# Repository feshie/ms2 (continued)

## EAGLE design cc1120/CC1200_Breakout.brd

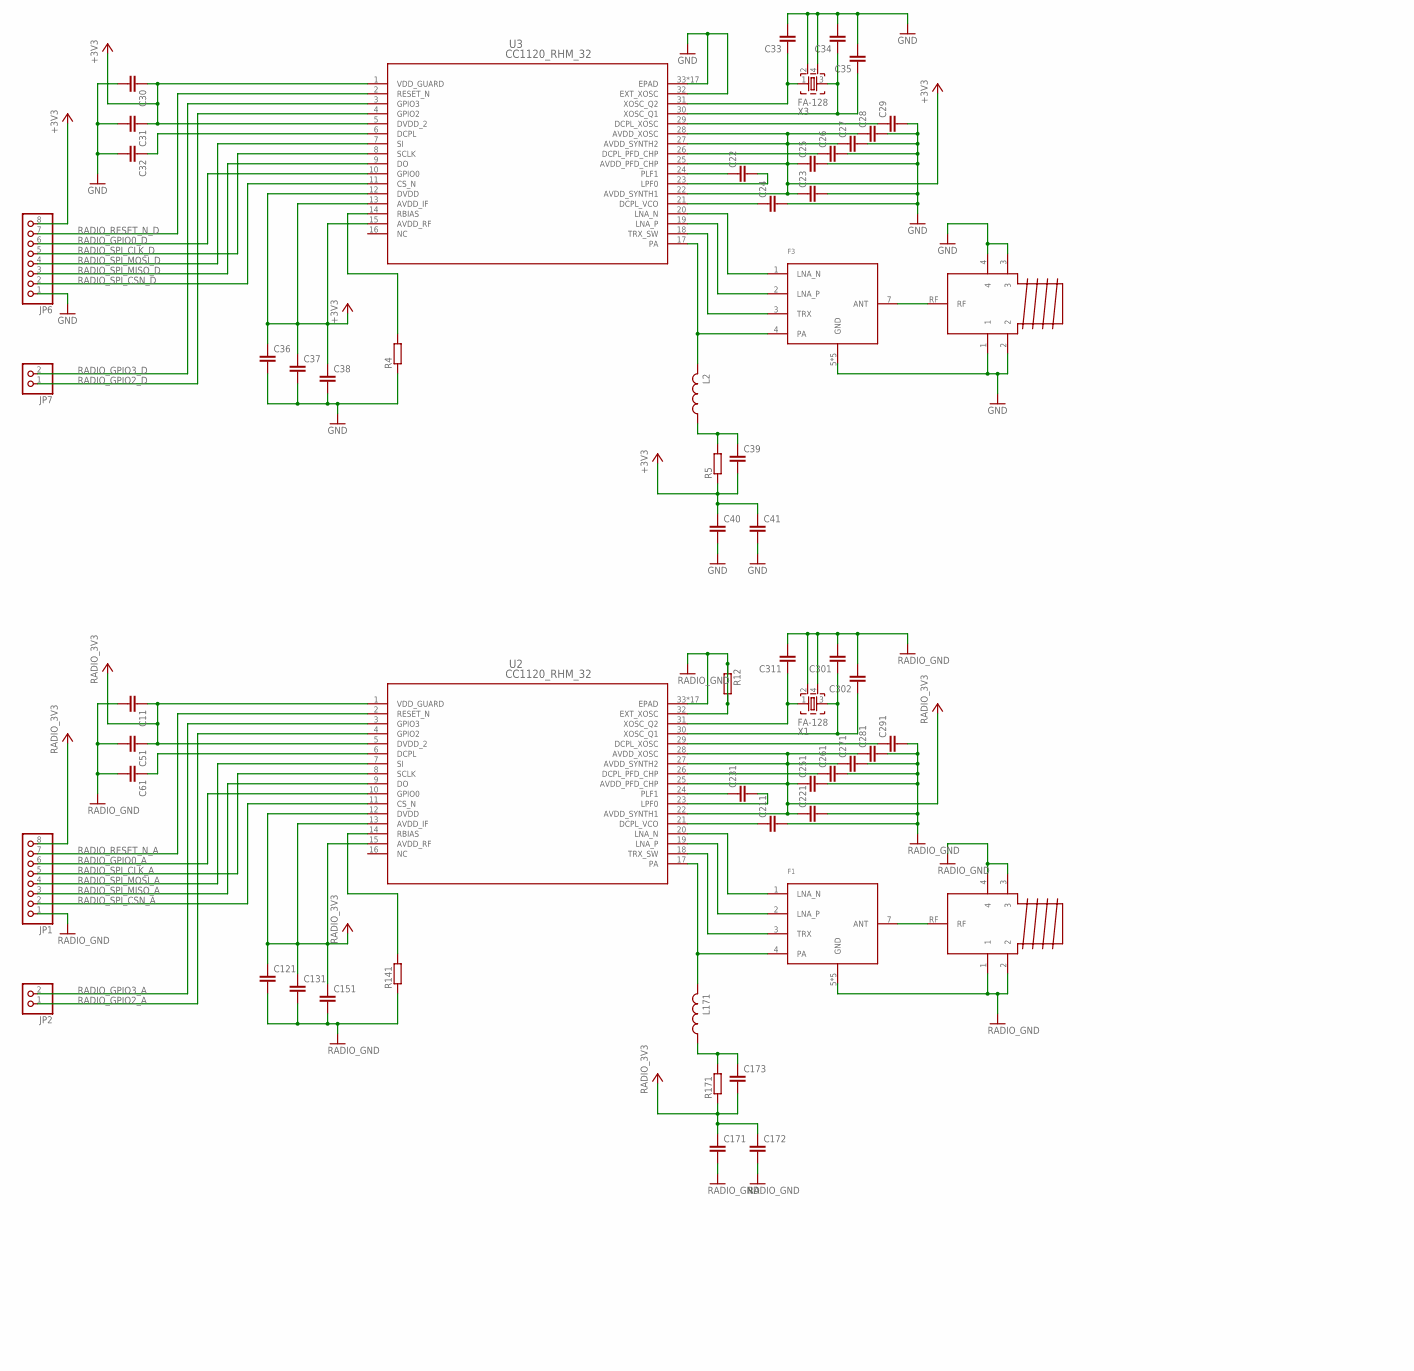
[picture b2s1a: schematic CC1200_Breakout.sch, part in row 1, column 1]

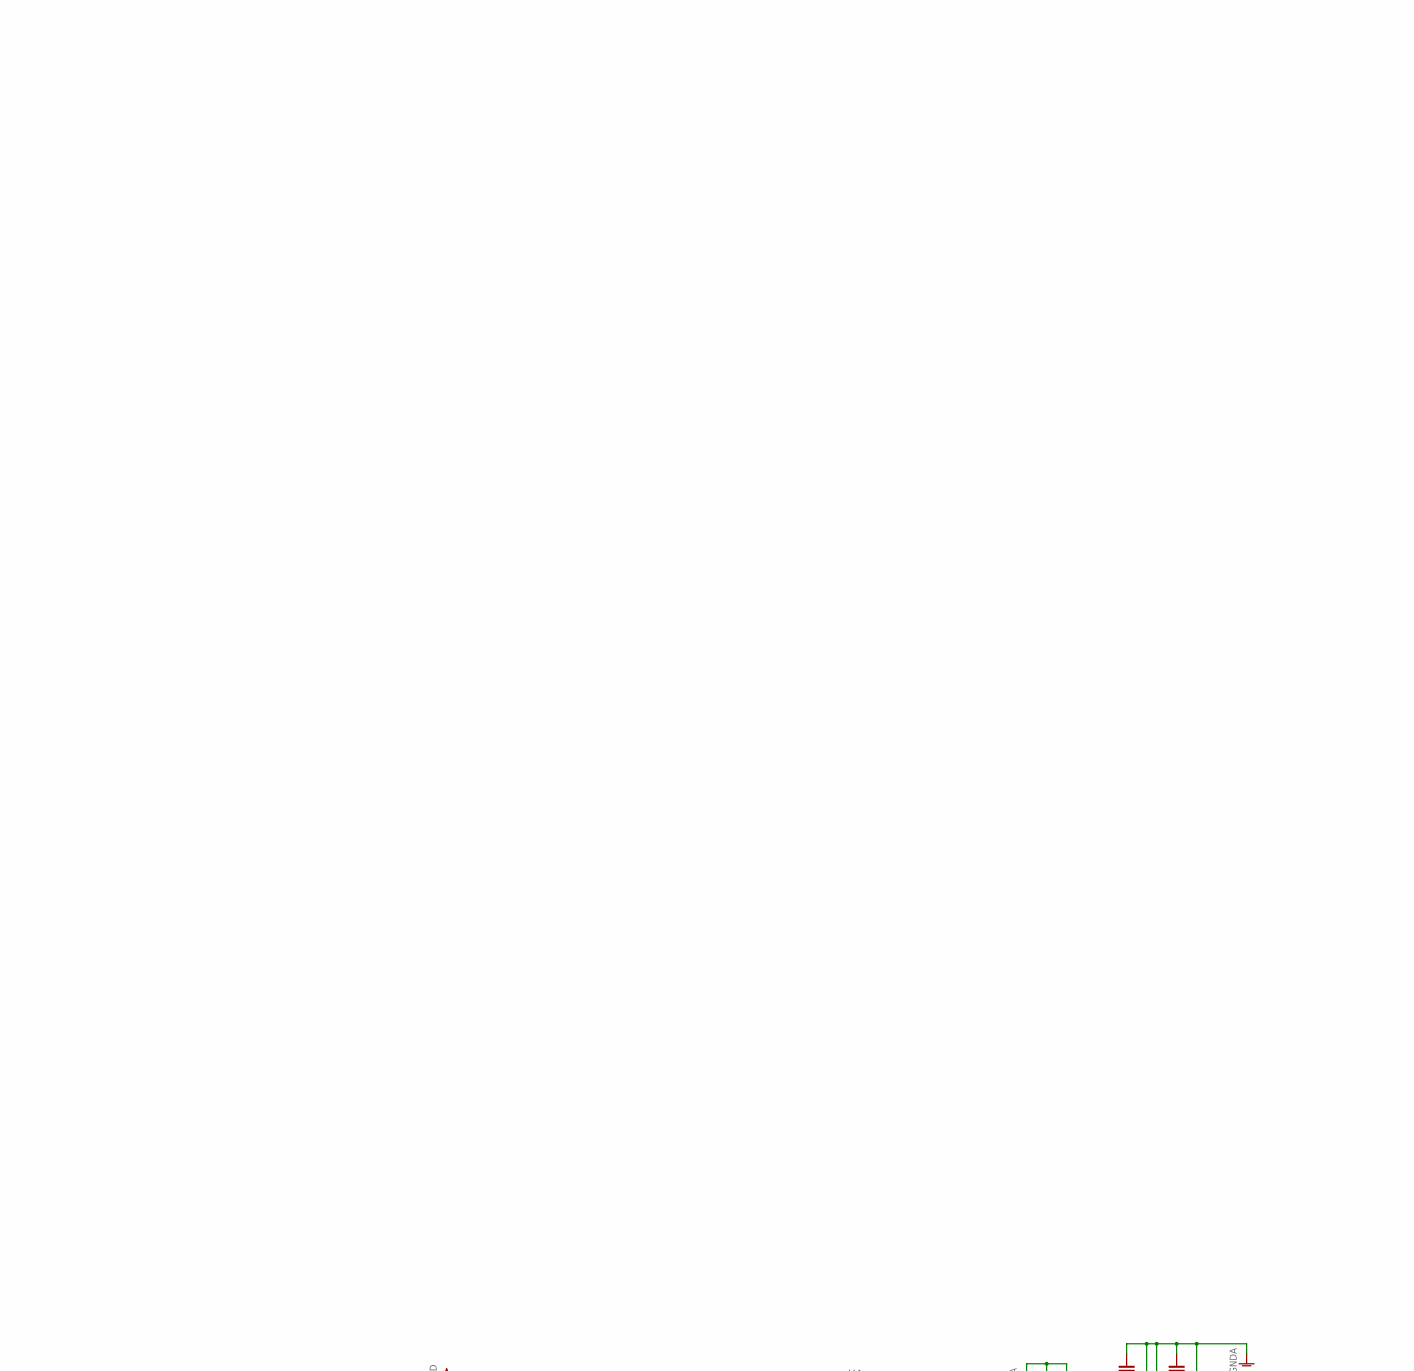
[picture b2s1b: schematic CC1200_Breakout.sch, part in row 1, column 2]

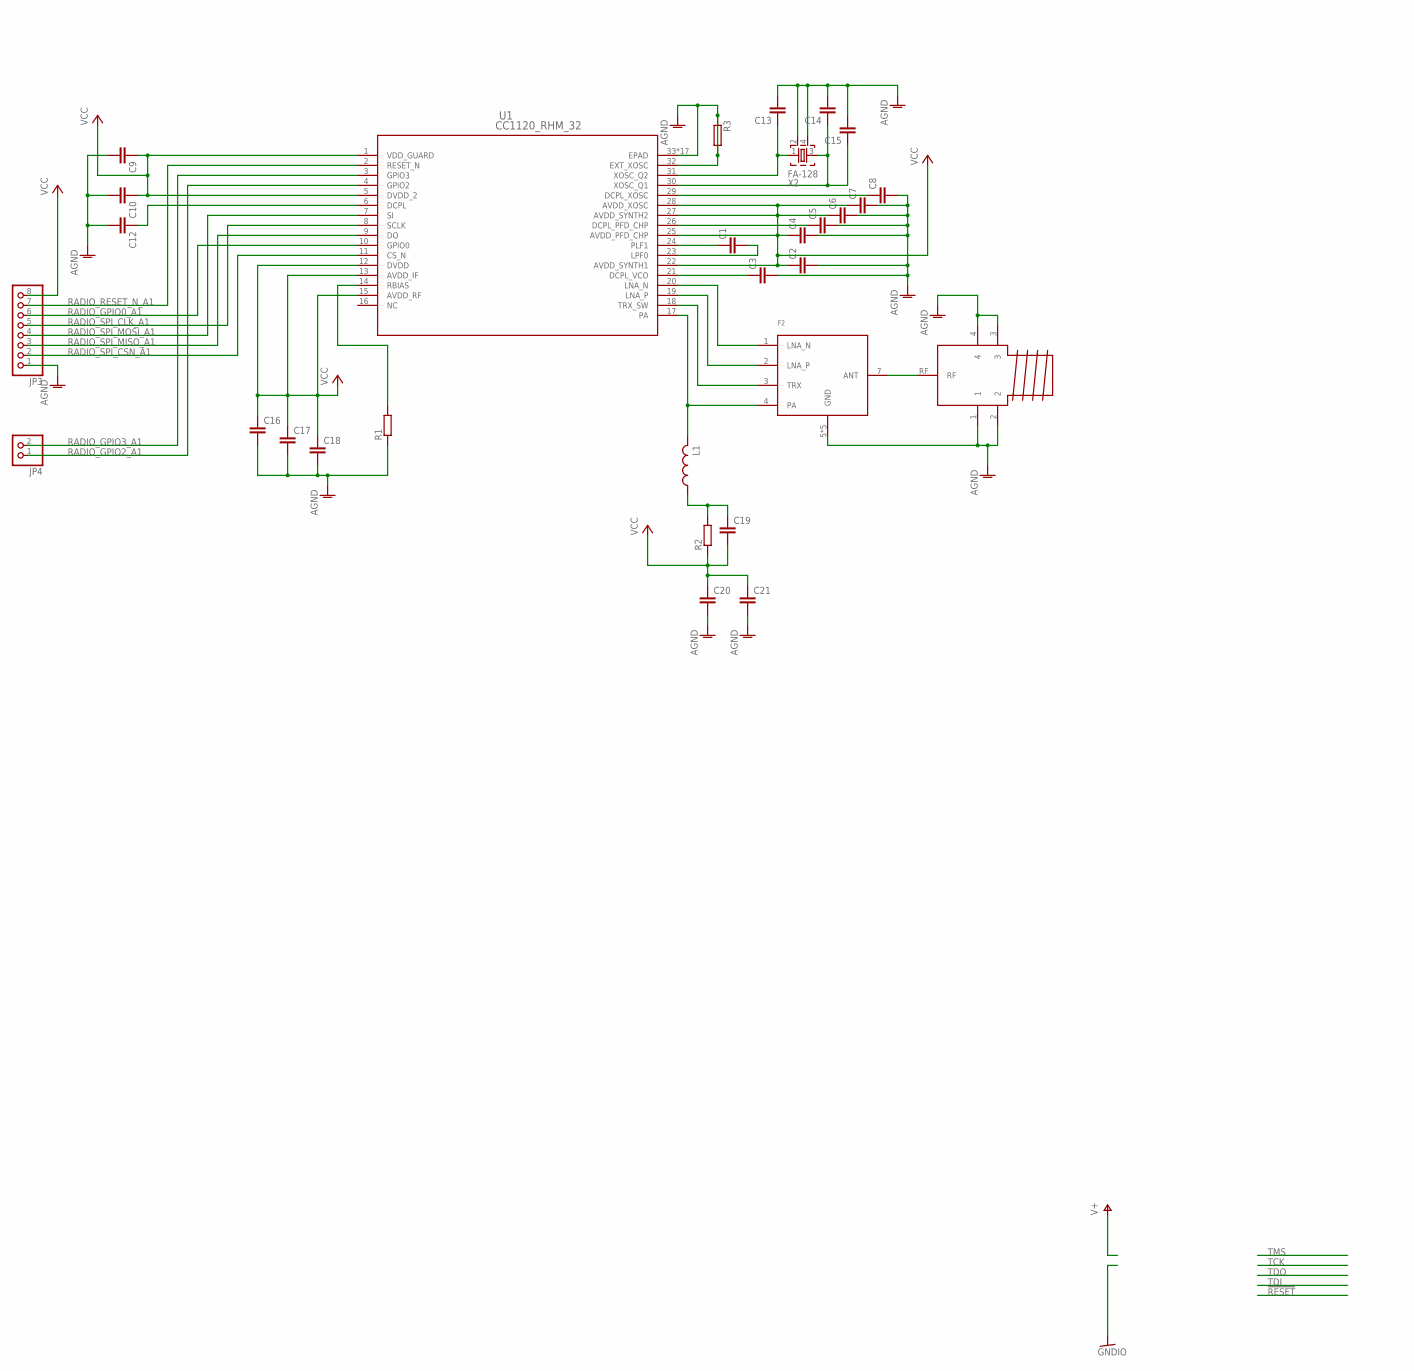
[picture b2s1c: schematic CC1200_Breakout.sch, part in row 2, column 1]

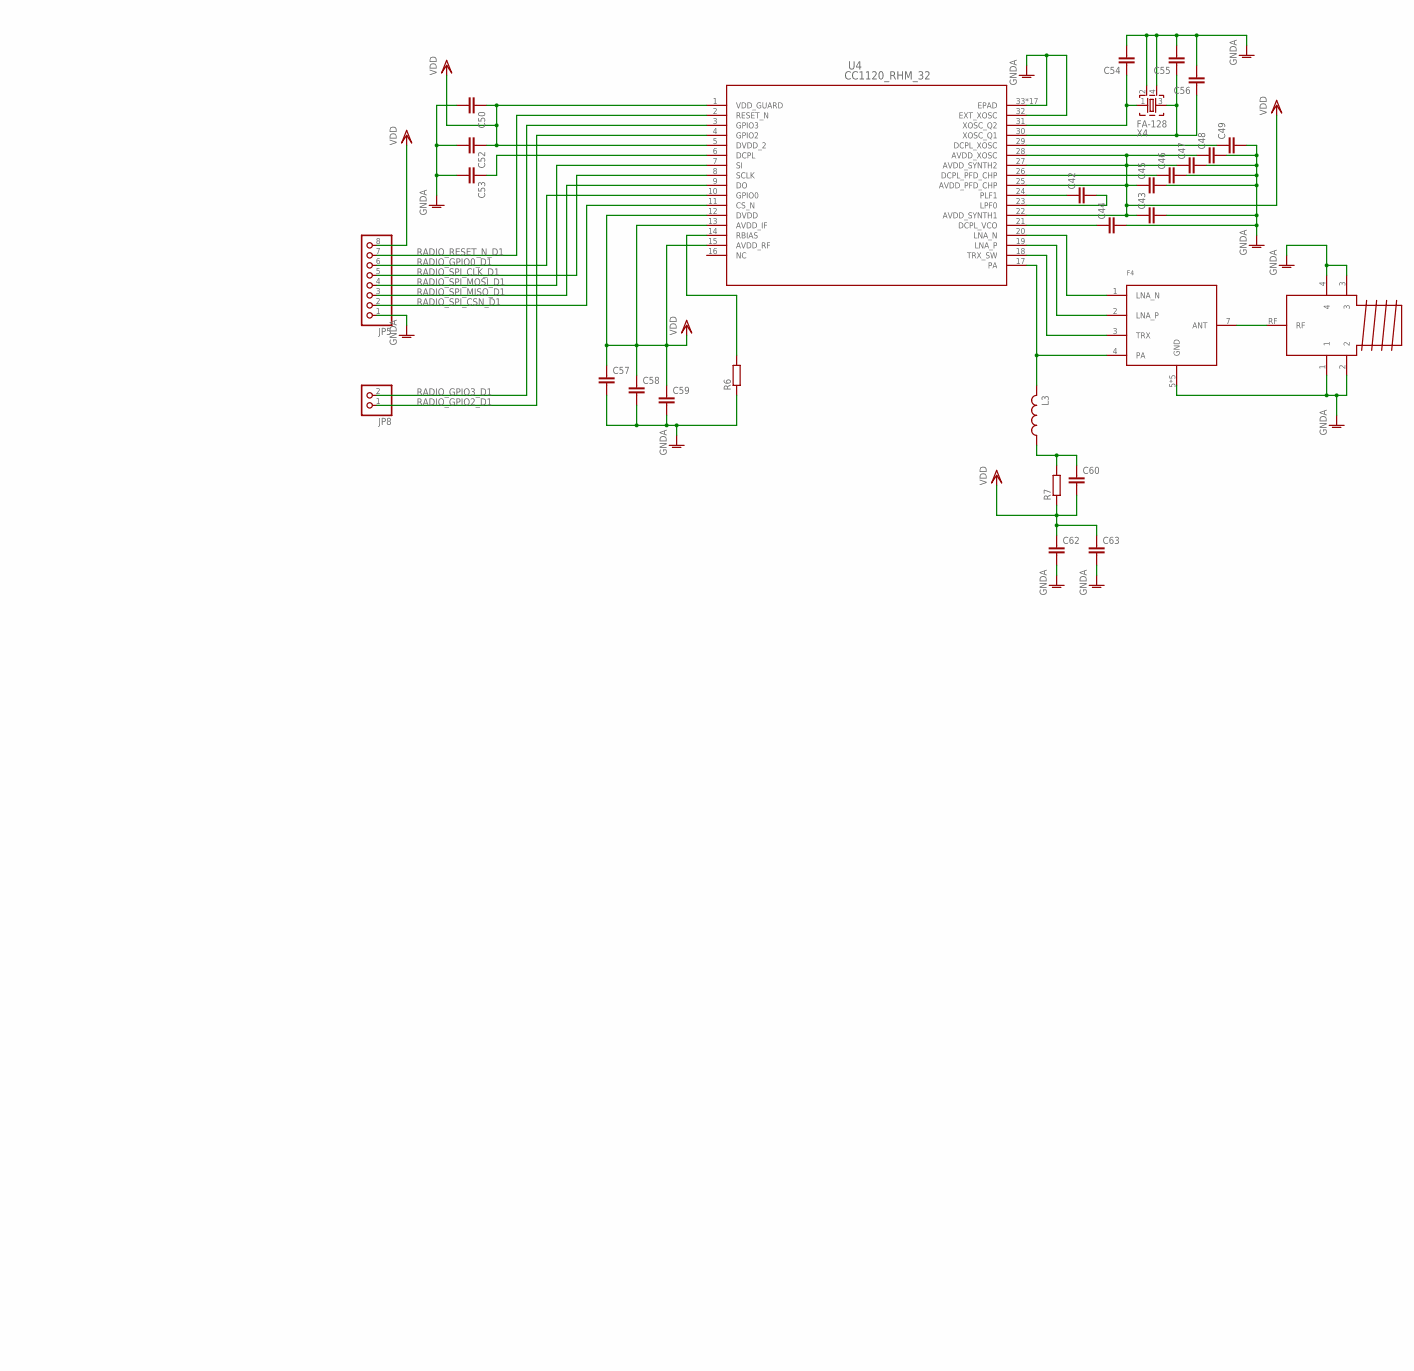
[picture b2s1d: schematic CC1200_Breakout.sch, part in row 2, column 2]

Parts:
ANT_1, ANT_2, ANT_3, ANT_868: SMA; JOHNSON_142-0701-806
C1, C2, C3, C4, C5, C6, C7, C8, C9, C10, C11, C12, C13, C14, C15, C16, C17, C18, C19, C20, C21, C51, C61, C121, C131, C151, C171, C172, C173, C211, C221, C231, C251, C261, C271, C281, C291, C301, C302, C311: C_EU0402S; C0402_SMALL
C22, C23, C24, C25, C26, C27, C28, C29, C30, C31, C32, C33, C34, C35, C36, C37, C38, C39, C40, C41, C42, C43, C44, C45, C46, C47, C48, C49, C50, C52, C53, C54, C55, C56, C57, C58, C59, C60, C62, C63: C_EUC0603S; C0603
F1, F2, F3, F4: 0900PC15J0013
JP1, JP3, JP5, JP6: PINHD-1X8; 1X08
JP2, JP4, JP7, JP8: PINHD-1X2; 1X02
L1, L171: L_US0402S; C0402_SMALL
L2, L3: L_US0603; C0603
R1, R2, R3, R12, R141, R171: R_EU; C0402_SMALL
R4, R5, R6, R7: R-EU_R0603; R0603
U1, U2, U3, U4: CC1120_RHM_32; RHM32_3P7X3P7
X1, X2, X3, X4: FA-128

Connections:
+3V3: C23.1, C25.1, C27.1, C28.1, C30.1, C31.1, C36.1, C37.1, C38.1, C39.2, C40.1, C41.1, JP6.8, R5.1, U3.1 (VDD_GUARD), U3.5 (DVDD_2), U3.12 (DVDD), U3.13 (AVDD_IF), U3.15 (AVDD_RF), U3.22 (AVDD_SYNTH1), U3.25 (AVDD_PFD_CHP), U3.27 (AVDD_SYNTH2), U3.28 (AVDD_XOSC)
AGND: ANT_1.1, ANT_1.2, ANT_1.3, ANT_1.4, C2.2, C3.2, C4.2, C5.2, C6.2, C7.2, C8.2, C9.2, C10.2, C12.2, C13.2, C14.2, C15.2, C16.2, C17.2, C18.2, C20.2, C21.2, F2.5 (GND), F2.6 (GND), F2.8 (GND), F2.9 (GND), F2.10 (GND), JP3.1, R1.1, R3.1, R3.2, U1.32 (EXT_XOSC), U1.33 (EPAD), U1.V (EPAD), U1.V_2 (EPAD), U1.V_3 (EPAD), U1.V_4 (EPAD), U1.V_5 (EPAD), U1.V_6 (EPAD), U1.V_7 (EPAD), U1.V_8 (EPAD), U1.V_9 (EPAD), U1.V_10 (EPAD), U1.V_11 (EPAD), U1.V_12 (EPAD), U1.V_13 (EPAD), U1.V_14 (EPAD), U1.V_15 (EPAD), U1.V_16 (EPAD), X2.2, X2.4
GND: ANT_2.1, ANT_2.2, ANT_2.3, ANT_2.4, C23.2, C24.2, C25.2, C26.2, C27.2, C28.2, C29.2, C30.2, C31.2, C32.2, C33.2, C34.2, C35.2, C36.2, C37.2, C38.2, C40.2, C41.2, F3.5 (GND), F3.6 (GND), F3.8 (GND), F3.9 (GND), F3.10 (GND), JP6.1, R4.1, U3.32 (EXT_XOSC), U3.33 (EPAD), U3.V (EPAD), U3.V_2 (EPAD), U3.V_3 (EPAD), U3.V_4 (EPAD), U3.V_5 (EPAD), U3.V_6 (EPAD), U3.V_7 (EPAD), U3.V_8 (EPAD), U3.V_9 (EPAD), U3.V_10 (EPAD), U3.V_11 (EPAD), U3.V_12 (EPAD), U3.V_13 (EPAD), U3.V_14 (EPAD), U3.V_15 (EPAD), U3.V_16 (EPAD), X3.2, X3.4
GNDA: ANT_3.1, ANT_3.2, ANT_3.3, ANT_3.4, C43.2, C44.2, C45.2, C46.2, C47.2, C48.2, C49.2, C50.2, C52.2, C53.2, C54.2, C55.2, C56.2, C57.2, C58.2, C59.2, C62.2, C63.2, F4.5 (GND), F4.6 (GND), F4.8 (GND), F4.9 (GND), F4.10 (GND), JP5.1, R6.1, U4.32 (EXT_XOSC), U4.33 (EPAD), U4.V (EPAD), U4.V_2 (EPAD), U4.V_3 (EPAD), U4.V_4 (EPAD), U4.V_5 (EPAD), U4.V_6 (EPAD), U4.V_7 (EPAD), U4.V_8 (EPAD), U4.V_9 (EPAD), U4.V_10 (EPAD), U4.V_11 (EPAD), U4.V_12 (EPAD), U4.V_13 (EPAD), U4.V_14 (EPAD), U4.V_15 (EPAD), U4.V_16 (EPAD), X4.2, X4.4
unnamed: C231.1, U2.24 (PLF1)
unnamed: C231.2, U2.23 (LPF0)
unnamed: C211.1, U2.21 (DCPL_VCO)
unnamed: C61.1, U2.6 (DCPL)
unnamed: C261.1, U2.26 (DCPL_PFD_CHP)
unnamed: C311.1, U2.31 (XOSC_Q2), X1.1
unnamed: C301.1, C302.1, U2.30 (XOSC_Q1), X1.3
unnamed: C291.1, U2.29 (DCPL_XOSC)
unnamed: F1.1 (LNA_N), U2.20 (LNA_N)
unnamed: F1.2 (LNA_P), U2.19 (LNA_P)
unnamed: ANT_868.RF, F1.7 (ANT)
unnamed: F1.3 (TRX), U2.18 (TRX_SW)
unnamed: R141.2, U2.14 (RBIAS)
unnamed: F1.4 (PA), L171.2, U2.17 (PA)
unnamed: C1.1, U1.24 (PLF1)
unnamed: C1.2, U1.23 (LPF0)
unnamed: C3.1, U1.21 (DCPL_VCO)
unnamed: C5.1, U1.26 (DCPL_PFD_CHP)
unnamed: C173.1, L171.1, R171.2
unnamed: C8.1, U1.29 (DCPL_XOSC)
unnamed: C12.1, U1.6 (DCPL)
unnamed: C13.1, U1.31 (XOSC_Q2), X2.1
unnamed: C14.1, C15.1, U1.30 (XOSC_Q1), X2.3
unnamed: R1.2, U1.14 (RBIAS)
unnamed: F2.1 (LNA_N), U1.20 (LNA_N)
unnamed: F2.2 (LNA_P), U1.19 (LNA_P)
unnamed: F2.3 (TRX), U1.18 (TRX_SW)
unnamed: F2.4 (PA), L1.2, U1.17 (PA)
unnamed: C19.1, L1.1, R2.2
unnamed: ANT_1.RF, F2.7 (ANT)
unnamed: C22.1, U3.24 (PLF1)
unnamed: C22.2, U3.23 (LPF0)
unnamed: C24.1, U3.21 (DCPL_VCO)
unnamed: C26.1, U3.26 (DCPL_PFD_CHP)
unnamed: C29.1, U3.29 (DCPL_XOSC)
unnamed: C32.1, U3.6 (DCPL)
unnamed: C33.1, U3.31 (XOSC_Q2), X3.1
unnamed: C34.1, C35.1, U3.30 (XOSC_Q1), X3.3
unnamed: R4.2, U3.14 (RBIAS)
unnamed: F3.1 (LNA_N), U3.20 (LNA_N)
unnamed: F3.2 (LNA_P), U3.19 (LNA_P)
unnamed: F3.3 (TRX), U3.18 (TRX_SW)
unnamed: F3.4 (PA), L2.2, U3.17 (PA)
unnamed: C39.1, L2.1, R5.2
unnamed: ANT_2.RF, F3.7 (ANT)
unnamed: C42.1, U4.24 (PLF1)
unnamed: C42.2, U4.23 (LPF0)
unnamed: C44.1, U4.21 (DCPL_VCO)
unnamed: C46.1, U4.26 (DCPL_PFD_CHP)
unnamed: C49.1, U4.29 (DCPL_XOSC)
unnamed: C53.1, U4.6 (DCPL)
unnamed: C54.1, U4.31 (XOSC_Q2), X4.1
unnamed: C55.1, C56.1, U4.30 (XOSC_Q1), X4.3
unnamed: R6.2, U4.14 (RBIAS)
unnamed: F4.1 (LNA_N), U4.20 (LNA_N)
unnamed: F4.2 (LNA_P), U4.19 (LNA_P)
unnamed: F4.3 (TRX), U4.18 (TRX_SW)
unnamed: F4.4 (PA), L3.2, U4.17 (PA)
unnamed: C60.1, L3.1, R7.2
unnamed: ANT_3.RF, F4.7 (ANT)
RADIO_3V3: C11.1, C51.1, C121.1, C131.1, C151.1, C171.1, C172.1, C173.2, C221.1, C251.1, C271.1, C281.1, JP1.8, R171.1, U2.1 (VDD_GUARD), U2.5 (DVDD_2), U2.12 (DVDD), U2.13 (AVDD_IF), U2.15 (AVDD_RF), U2.22 (AVDD_SYNTH1), U2.25 (AVDD_PFD_CHP), U2.27 (AVDD_SYNTH2), U2.28 (AVDD_XOSC)
RADIO_GND: ANT_868.1, ANT_868.2, ANT_868.3, ANT_868.4, C11.2, C51.2, C61.2, C121.2, C131.2, C151.2, C171.2, C172.2, C211.2, C221.2, C251.2, C261.2, C271.2, C281.2, C291.2, C301.2, C302.2, C311.2, F1.5 (GND), F1.6 (GND), F1.8 (GND), F1.9 (GND), F1.10 (GND), JP1.1, R12.1, R12.2, R141.1, U2.32 (EXT_XOSC), U2.33 (EPAD), U2.V (EPAD), U2.V_2 (EPAD), U2.V_3 (EPAD), U2.V_4 (EPAD), U2.V_5 (EPAD), U2.V_6 (EPAD), U2.V_7 (EPAD), U2.V_8 (EPAD), U2.V_9 (EPAD), U2.V_10 (EPAD), U2.V_11 (EPAD), U2.V_12 (EPAD), U2.V_13 (EPAD), U2.V_14 (EPAD), U2.V_15 (EPAD), U2.V_16 (EPAD), X1.2, X1.4
RADIO_GPIO0_A: JP1.6, U2.10 (GPIO0)
RADIO_GPIO0_A1: JP3.6, U1.10 (GPIO0)
RADIO_GPIO0_D: JP6.6, U3.10 (GPIO0)
RADIO_GPIO0_D1: JP5.6, U4.10 (GPIO0)
RADIO_GPIO2_A: JP2.1, U2.4 (GPIO2)
RADIO_GPIO2_A1: JP4.1, U1.4 (GPIO2)
RADIO_GPIO2_D: JP7.1, U3.4 (GPIO2)
RADIO_GPIO2_D1: JP8.1, U4.4 (GPIO2)
RADIO_GPIO3_A: JP2.2, U2.3 (GPIO3)
RADIO_GPIO3_A1: JP4.2, U1.3 (GPIO3)
RADIO_GPIO3_D: JP7.2, U3.3 (GPIO3)
RADIO_GPIO3_D1: JP8.2, U4.3 (GPIO3)
RADIO_RESET_N_A: JP1.7, U2.2 (RESET_N)
RADIO_RESET_N_A1: JP3.7, U1.2 (RESET_N)
RADIO_RESET_N_D: JP6.7, U3.2 (RESET_N)
RADIO_RESET_N_D1: JP5.7, U4.2 (RESET_N)
RADIO_SPI_CLK_A: JP1.5, U2.8 (SCLK)
RADIO_SPI_CLK_A1: JP3.5, U1.8 (SCLK)
RADIO_SPI_CLK_D: JP6.5, U3.8 (SCLK)
RADIO_SPI_CLK_D1: JP5.5, U4.8 (SCLK)
RADIO_SPI_CSN_A: JP1.2, U2.11 (CS_N)
RADIO_SPI_CSN_A1: JP3.2, U1.11 (CS_N)
RADIO_SPI_CSN_D: JP6.2, U3.11 (CS_N)
RADIO_SPI_CSN_D1: JP5.2, U4.11 (CS_N)
RADIO_SPI_MISO_A: JP1.3, U2.9 (DO)
RADIO_SPI_MISO_A1: JP3.3, U1.9 (DO)
RADIO_SPI_MISO_D: JP6.3, U3.9 (DO)
RADIO_SPI_MISO_D1: JP5.3, U4.9 (DO)
RADIO_SPI_MOSI_A: JP1.4, U2.7 (SI)
RADIO_SPI_MOSI_A1: JP3.4, U1.7 (SI)
RADIO_SPI_MOSI_D: JP6.4, U3.7 (SI)
RADIO_SPI_MOSI_D1: JP5.4, U4.7 (SI)
VCC: C2.1, C4.1, C6.1, C7.1, C9.1, C10.1, C16.1, C17.1, C18.1, C19.2, C20.1, C21.1, JP3.8, R2.1, U1.1 (VDD_GUARD), U1.5 (DVDD_2), U1.12 (DVDD), U1.13 (AVDD_IF), U1.15 (AVDD_RF), U1.22 (AVDD_SYNTH1), U1.25 (AVDD_PFD_CHP), U1.27 (AVDD_SYNTH2), U1.28 (AVDD_XOSC)
VDD: C43.1, C45.1, C47.1, C48.1, C50.1, C52.1, C57.1, C58.1, C59.1, C60.2, C62.1, C63.1, JP5.8, R7.1, U4.1 (VDD_GUARD), U4.5 (DVDD_2), U4.12 (DVDD), U4.13 (AVDD_IF), U4.15 (AVDD_RF), U4.22 (AVDD_SYNTH1), U4.25 (AVDD_PFD_CHP), U4.27 (AVDD_SYNTH2), U4.28 (AVDD_XOSC)

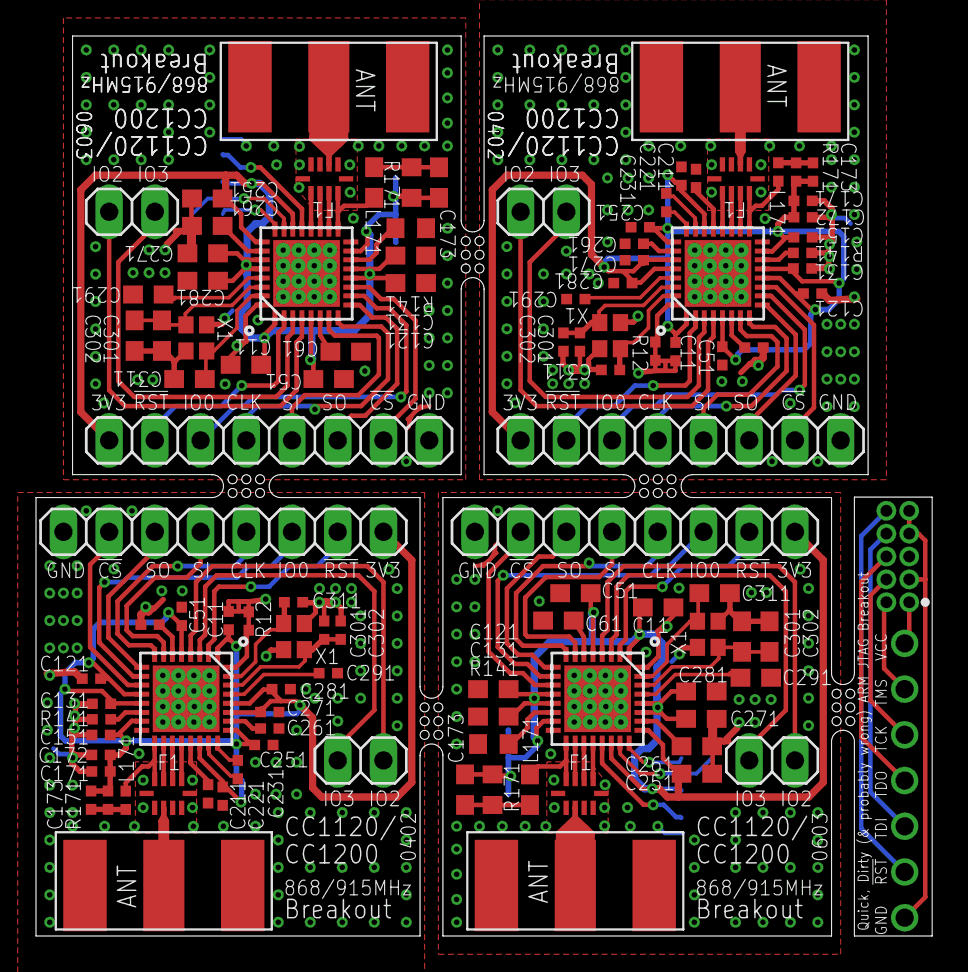
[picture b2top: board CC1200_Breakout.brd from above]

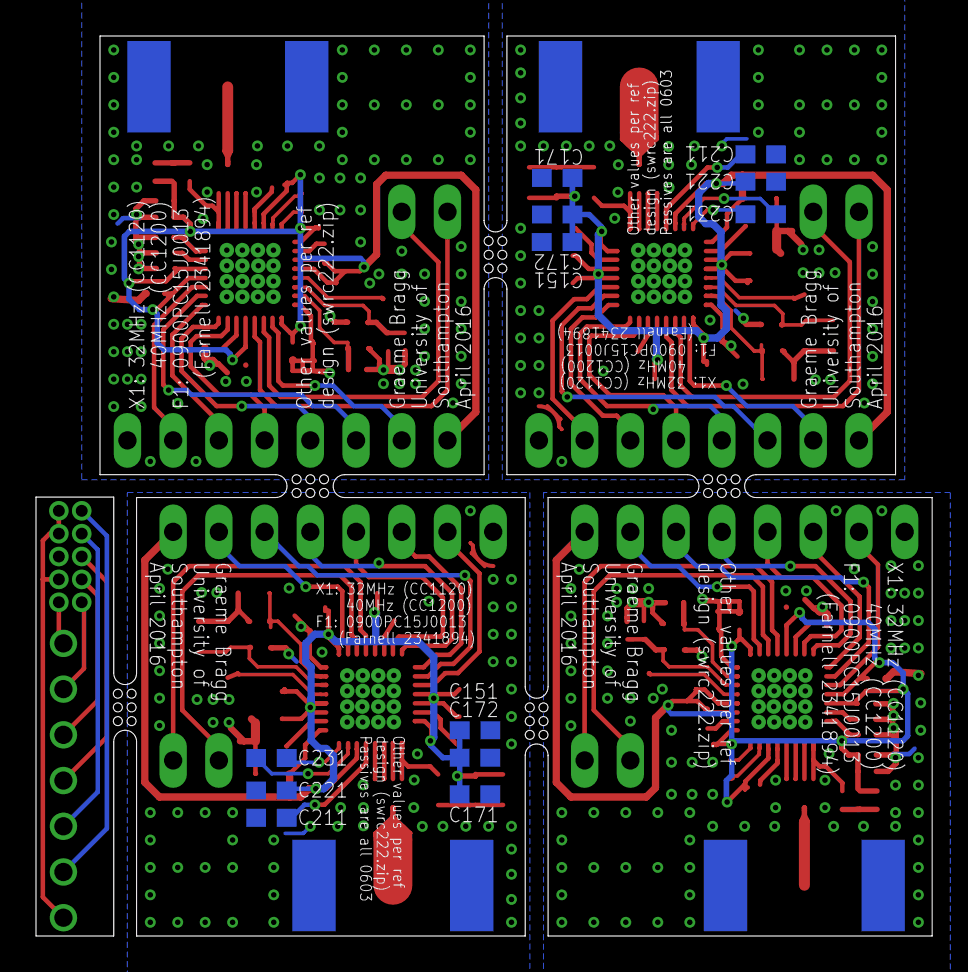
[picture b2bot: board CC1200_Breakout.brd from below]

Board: 4 copper layers, 49.8 x 50.0 mm, 118 parts (12 on the bottom side), 100 nets.

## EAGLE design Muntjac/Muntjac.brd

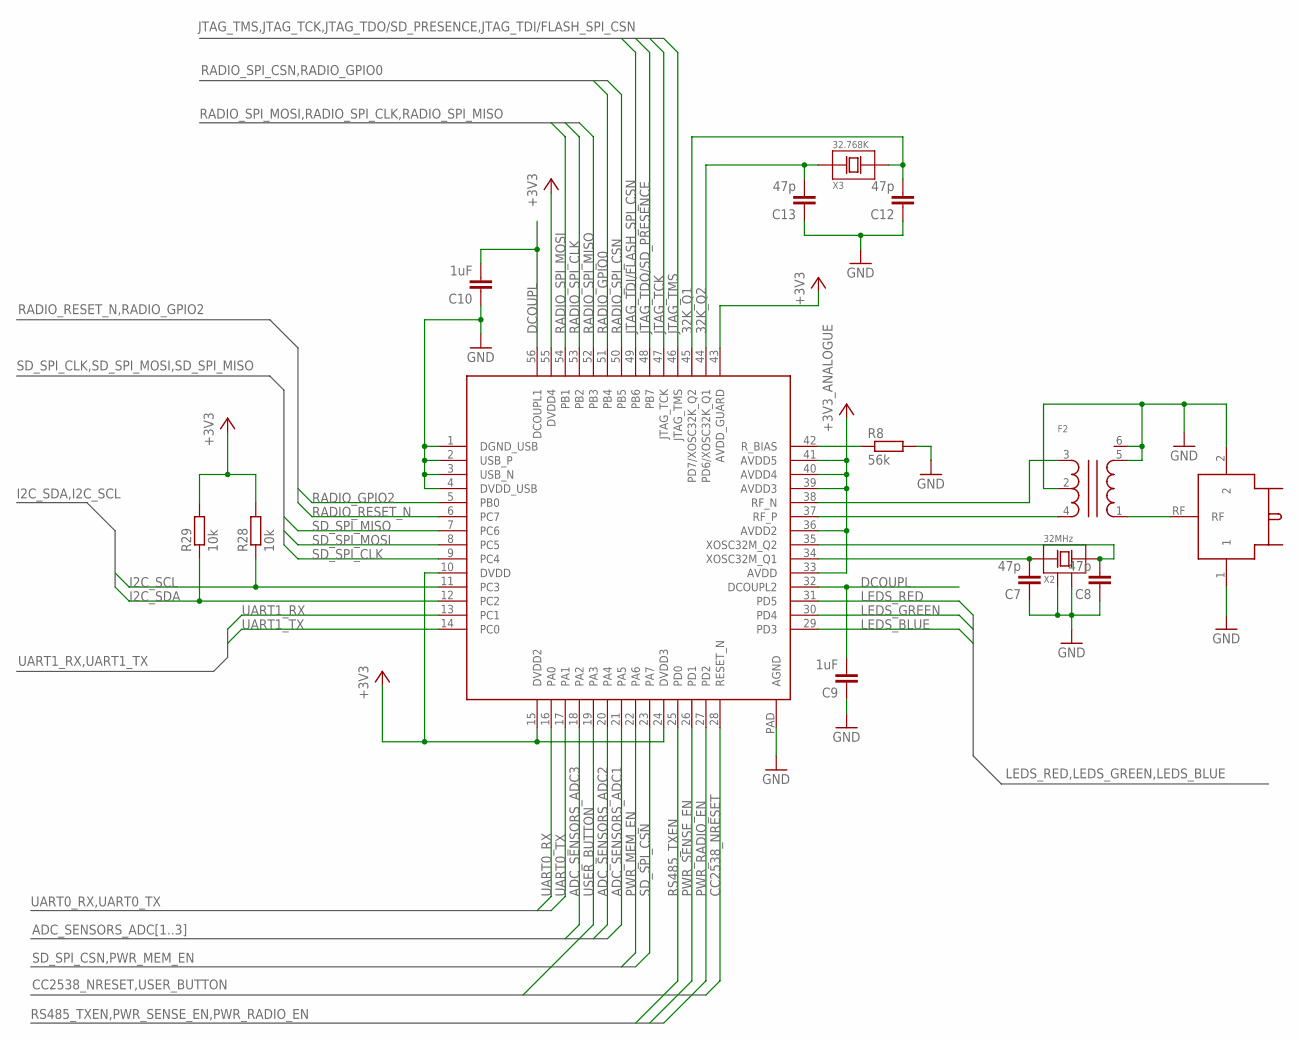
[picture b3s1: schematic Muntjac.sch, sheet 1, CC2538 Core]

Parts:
ANT: UFL; UFL-HIROSE
C7, C8, C12, C13: 47p; C0603
C9, C10: 1uF; C0603
F2: BALUN-2.4G; 2450BM15A0015
R8: 56k; R0603
R28, R29: 10k; R0603
U1: CC2538; QFN56
X2: 32MHz; XTAL-3.2X2.5
X3: 32.768K; XTAL-3.2X1.5

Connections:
2.4G: ANT.RF, F2.1
32K_Q1: C12.2, U1.45 (PD7/XOSC32K_Q2), X3.2 (3)
32K_Q2: C13.2, U1.44 (PD6/XOSC32K_Q1), X3.1
32M_Q1: C7.2, U1.34 (XOSC32M_Q1), X2.1
32M_Q2: C8.2, U1.35 (XOSC32M_Q2), X2.3
+3V3: R28.2, R29.2, U1.10 (DVDD), U1.15 (DVDD2), U1.24 (DVDD3), U1.43 (AVDD_GUARD), U1.55 (DVDD4); also elsewhere on the board
+3V3_ANALOGUE: U1.33 (AVDD), U1.36 (AVDD2), U1.39 (AVDD3), U1.40 (AVDD4), U1.41 (AVDD5); also elsewhere on the board
ADC_SENSORS_ADC1: U1.21 (PA5); also elsewhere on the board
ADC_SENSORS_ADC2: U1.20 (PA4); also elsewhere on the board
ADC_SENSORS_ADC3: U1.18 (PA2); also elsewhere on the board
CC2538_NRESET: U1.28 (RESET_N); also elsewhere on the board
DCOUPL: C9.2, C10.2, U1.32 (DCOUPL2), U1.56 (DCOUPL1)
GND: ANT.1, ANT.2, C7.1, C8.1, C9.1, C10.1, C12.1, C13.1, F2.2, F2.5, F2.6, R8.2, U1.1 (DGND_USB), U1.2 (USB_P), U1.3 (USB_N), U1.4 (DVDD_USB), U1.PAD (AGND), X2.2, X2.4; also elsewhere on the board
I2C_SCL: R28.1, U1.11 (PC3); also elsewhere on the board
I2C_SDA: R29.1, U1.12 (PC2); also elsewhere on the board
JTAG_TCK: U1.47 (JTAG_TCK); also elsewhere on the board
JTAG_TDI/FLASH_SPI_CSN: U1.49 (PB6); also elsewhere on the board
JTAG_TDO/SD_PRESENCE: U1.48 (PB7); also elsewhere on the board
JTAG_TMS: U1.46 (JTAG_TMS); also elsewhere on the board
LEDS_BLUE: U1.29 (PD3); also elsewhere on the board
LEDS_GREEN: U1.30 (PD4); also elsewhere on the board
LEDS_RED: U1.31 (PD5); also elsewhere on the board
unnamed: R8.1, U1.42 (R_BIAS)
unnamed: F2.4, U1.37 (RF_P)
unnamed: F2.3, U1.38 (RF_N)
PWR_MEM_EN: U1.22 (PA6); also elsewhere on the board
PWR_RADIO_EN: U1.27 (PD2); also elsewhere on the board
PWR_SENSE_EN: U1.26 (PD1); also elsewhere on the board
RADIO_GPIO0: U1.51 (PB4); also elsewhere on the board
RADIO_GPIO2: U1.5 (PB0); also elsewhere on the board
RADIO_RESET_N: U1.6 (PC7); also elsewhere on the board
RADIO_SPI_CLK: U1.53 (PB2); also elsewhere on the board
RADIO_SPI_CSN: U1.50 (PB5); also elsewhere on the board
RADIO_SPI_MISO: U1.52 (PB3); also elsewhere on the board
RADIO_SPI_MOSI: U1.54 (PB1); also elsewhere on the board
RS485_TXEN: U1.25 (PD0); also elsewhere on the board
SD_SPI_CLK: U1.9 (PC4); also elsewhere on the board
SD_SPI_CSN: U1.23 (PA7); also elsewhere on the board
SD_SPI_MISO: U1.7 (PC6); also elsewhere on the board
SD_SPI_MOSI: U1.8 (PC5); also elsewhere on the board
UART0_RX: U1.16 (PA0); also elsewhere on the board
UART0_TX: U1.17 (PA1); also elsewhere on the board
UART1_RX: U1.13 (PC1); also elsewhere on the board
UART1_TX: U1.14 (PC0); also elsewhere on the board
USER_BUTTON: U1.19 (PA3); also elsewhere on the board

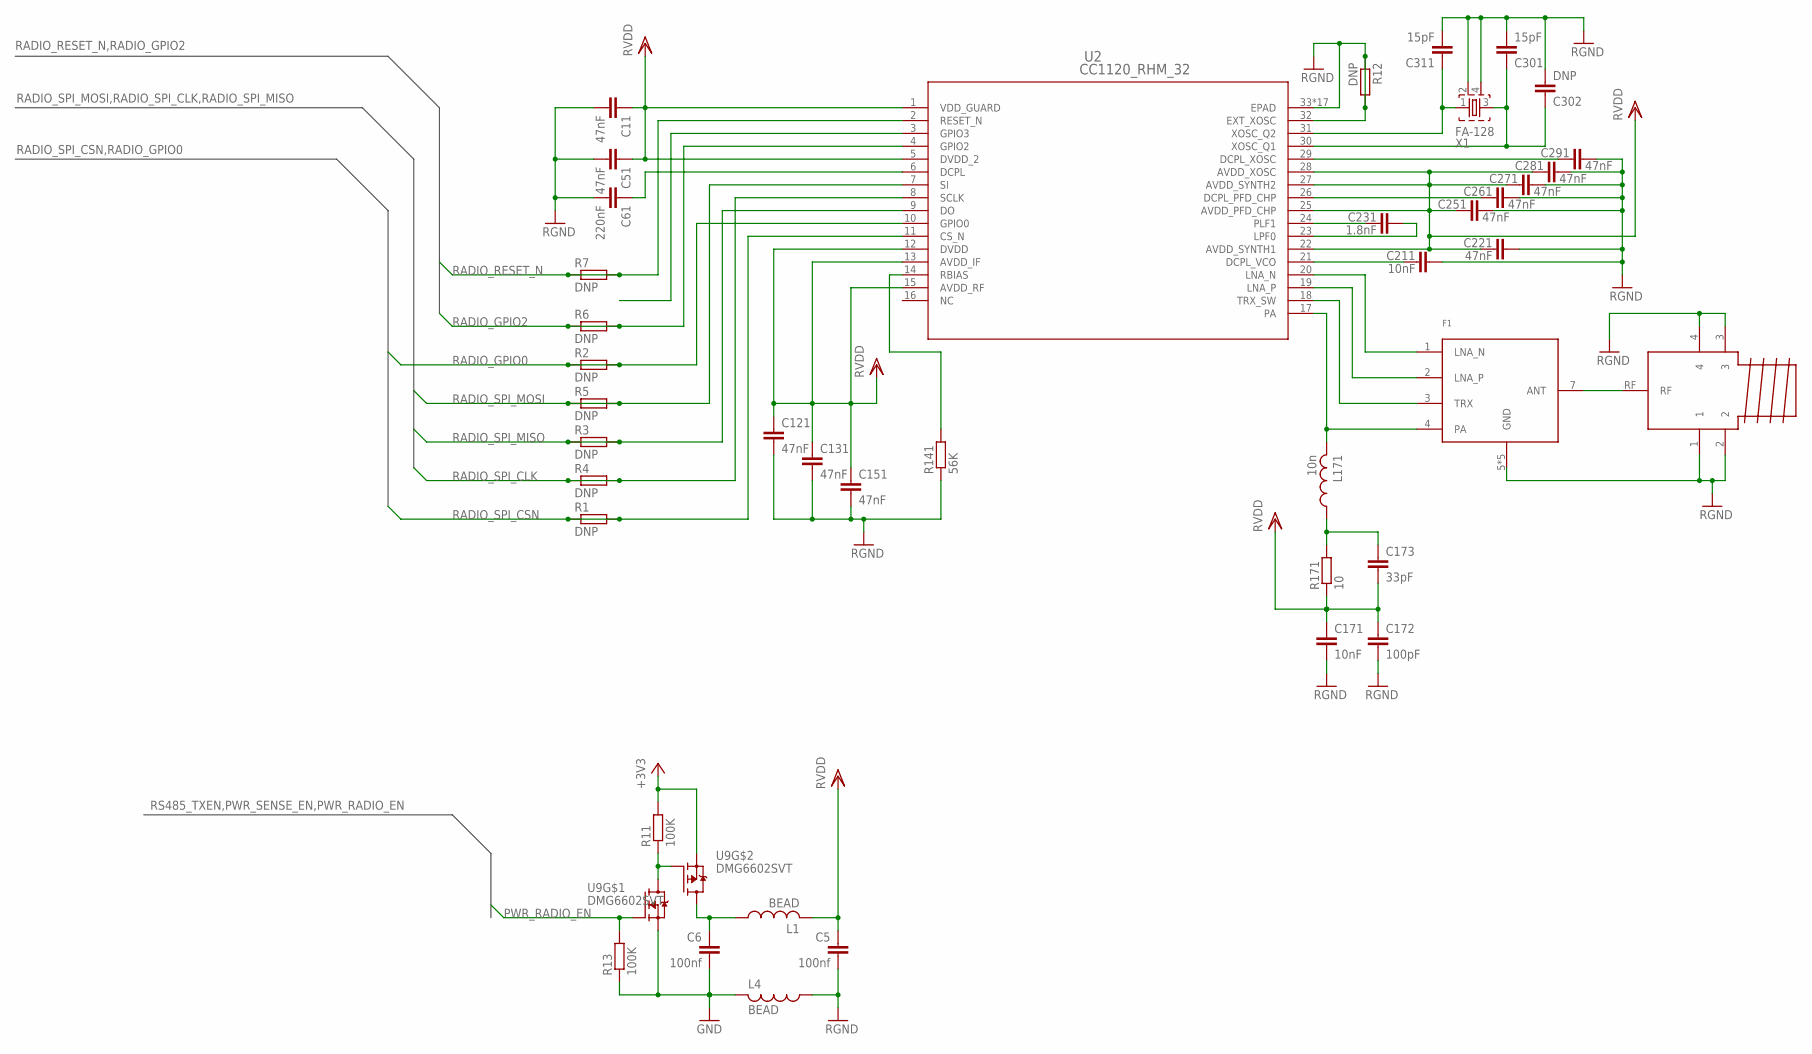
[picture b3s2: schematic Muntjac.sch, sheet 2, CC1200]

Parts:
ANT_868: SMA; JOHNSON_142-0701-806
C5, C6: 100nf; C0603
C11, C51, C121, C131, C151, C221, C251, C261, C271, C281, C291: 47nF; C0402_SMALL
C61: 220nF; C0402_SMALL
C171, C211: 10nF; C0402_SMALL
C172: 100pF; C0402_SMALL
C173: 33pF; C0402_SMALL
C231: 1.8nF; C0402_SMALL
C301, C311: 15pF; C0402_SMALL
C302: DNP; C0402_SMALL
F1: 0900PC15J0013
L1, L4: BEAD; C0603
L171: 10n; C0402_SMALL
R1, R2, R3, R4, R5, R6, R7: DNP; R0402
R11, R13: 100K; R0603
R12: DNP; C0402_SMALL
R141: 56K; C0402_SMALL
R171: 10; C0402_SMALL
U2: CC1120_RHM_32; RHM32_3P7X3P7
U9: DMG6602SVT; TSOT26
X1: FA-128

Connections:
+3V3: R11.2, U9.P$2 (S); also elsewhere on the board
GND: C6.2, L4.2, R13.1, U9.P$5 (S); also elsewhere on the board
unnamed: C231.1, U2.24 (PLF1)
unnamed: C231.2, U2.23 (LPF0)
unnamed: C211.1, U2.21 (DCPL_VCO)
unnamed: C61.1, U2.6 (DCPL)
unnamed: C261.1, U2.26 (DCPL_PFD_CHP)
unnamed: C311.1, U2.31 (XOSC_Q2), X1.1
unnamed: C301.1, C302.1, U2.30 (XOSC_Q1), X1.3
unnamed: C291.1, U2.29 (DCPL_XOSC)
unnamed: F1.1 (LNA_N), U2.20 (LNA_N)
unnamed: F1.2 (LNA_P), U2.19 (LNA_P)
unnamed: ANT_868.RF, F1.7 (ANT)
unnamed: F1.3 (TRX), U2.18 (TRX_SW)
unnamed: R141.2, U2.14 (RBIAS)
unnamed: F1.4 (PA), L171.2, U2.17 (PA)
unnamed: C173.1, L171.1, R171.2
unnamed: C6.1, L1.1, U9.P$4 (D)
unnamed: R11.1, U9.P$3 (G), U9.P$6 (D)
PWR_RADIO_EN: R13.2, U9.P$1 (G); also elsewhere on the board
RADIO_GPIO0: R2.1, R2.2, U2.10 (GPIO0); also elsewhere on the board
RADIO_GPIO2: R6.1, R6.2, U2.4 (GPIO2); also elsewhere on the board
RADIO_GPIO3: U2.3 (GPIO3)
RADIO_RESET_N: R7.1, R7.2, U2.2 (RESET_N); also elsewhere on the board
RADIO_SPI_CLK: R4.1, R4.2, U2.8 (SCLK); also elsewhere on the board
RADIO_SPI_CSN: R1.1, R1.2, U2.11 (CS_N); also elsewhere on the board
RADIO_SPI_MISO: R3.1, R3.2, U2.9 (DO); also elsewhere on the board
RADIO_SPI_MOSI: R5.1, R5.2, U2.7 (SI); also elsewhere on the board
RGND: ANT_868.1, ANT_868.2, ANT_868.3, ANT_868.4, C5.2, C11.2, C51.2, C61.2, C121.2, C131.2, C151.2, C171.2, C172.2, C211.2, C221.2, C251.2, C261.2, C271.2, C281.2, C291.2, C301.2, C302.2, C311.2, F1.5 (GND), F1.6 (GND), F1.8 (GND), F1.9 (GND), F1.10 (GND), L4.1, R12.1, R12.2, R141.1, U2.32 (EXT_XOSC), U2.33 (EPAD), U2.V (EPAD), U2.V_2 (EPAD), U2.V_3 (EPAD), U2.V_4 (EPAD), U2.V_5 (EPAD), U2.V_6 (EPAD), U2.V_7 (EPAD), U2.V_8 (EPAD), U2.V_9 (EPAD), U2.V_10 (EPAD), U2.V_11 (EPAD), U2.V_12 (EPAD), U2.V_13 (EPAD), U2.V_14 (EPAD), U2.V_15 (EPAD), U2.V_16 (EPAD), X1.2, X1.4
RVDD: C5.1, C11.1, C51.1, C121.1, C131.1, C151.1, C171.1, C172.1, C173.2, C221.1, C251.1, C271.1, C281.1, L1.2, R171.1, U2.1 (VDD_GUARD), U2.5 (DVDD_2), U2.12 (DVDD), U2.13 (AVDD_IF), U2.15 (AVDD_RF), U2.22 (AVDD_SYNTH1), U2.25 (AVDD_PFD_CHP), U2.27 (AVDD_SYNTH2), U2.28 (AVDD_XOSC)
